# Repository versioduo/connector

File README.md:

# ⚡ V2 Link and Power connectors

# Copying
Anyone can use this public domain work without having to seek authorisation, no one can ever own it.

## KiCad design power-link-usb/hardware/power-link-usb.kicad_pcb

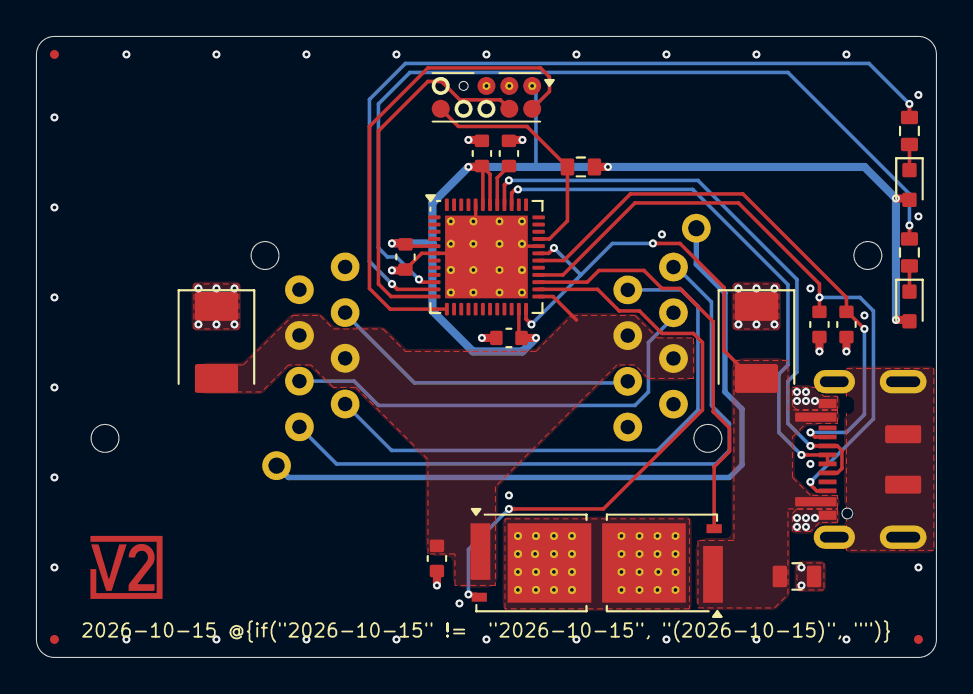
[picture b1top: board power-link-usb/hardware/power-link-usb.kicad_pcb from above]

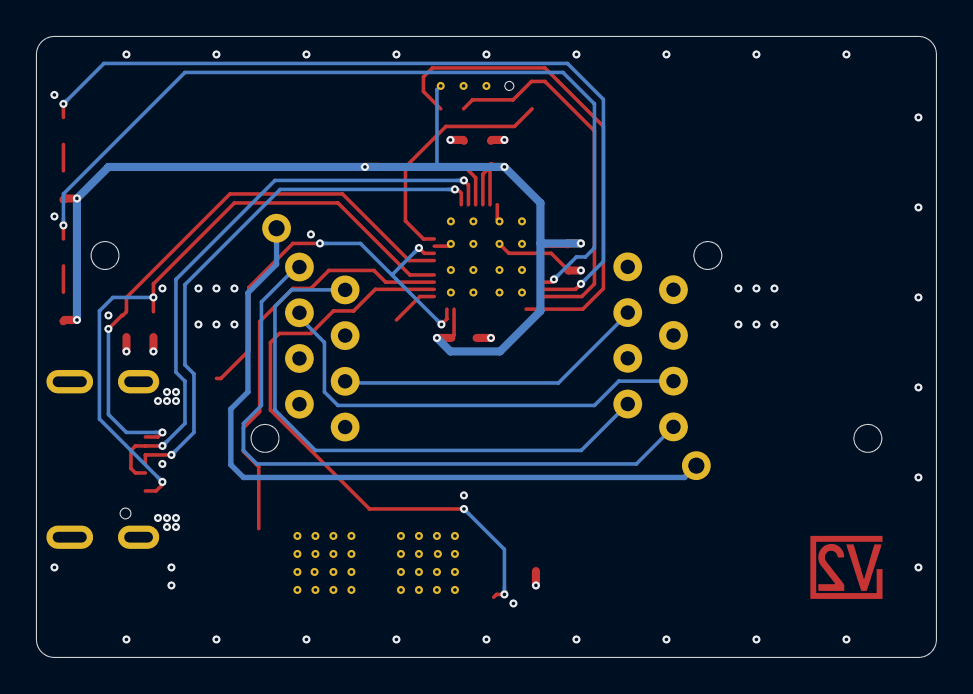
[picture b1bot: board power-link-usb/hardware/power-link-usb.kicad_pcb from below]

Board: 4 copper layers, 50.0 x 34.5 mm, 28 parts (2 on the bottom side), 24 nets.

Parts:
C201: 10u; C_1608
C202, C204, C205: 0u1; C_1608
C203: 10u; C_2012
C206: 1u; C_1608
C207, C208: 390p; C_1608
D201: Orange; LED_1608
D202: Red; LED_1608
FID101, FID102, FID103: Fiducial_Paste; Fiducial_0.5mm_Mask1mm_Paste
ICON101: V2-logo; Logo_Small
INFO101: Revision
INFO102: Layer_Numbers-4
J101, J102: NE8FAH
J201: DX07S016JA3; JAE_DX07S016JA3-PD
J202: Cortex
Q201, Q202: BSC010N04LS; TDSON-8-FL
R201, R202: 330R; R_1608
R203: 10k; R_1608
TVS101, TVS201: SMBJ33CA; D_SMB
U201: CYPM1311-48LDXI; QFN-48-1EP_6x6mm_P0.4mm_EP4.6x4.6mm

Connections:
/+VLINK: C206.1, J101.4, J101.5, J102.4, J102.5, Q202.1 (S), TVS101.2 (A), U201.25 (VBUS_OUT_NGDO)
/Power USB/+VBUS: C203.1, J201.V (VBUS), Q201.1 (S), TVS201.2 (A), U201.24 (VBUS_IN_NGDO), U201.31 (VBUS_C)
/Power USB/+VCORE: C205.2, U201.41 (VCCD)
/Power USB/+VSUPPLY: C201.1, C202.1, C204.1, D201.2 (A), D202.2 (A), J202.1 (VCC), R203.2, U201.5 (VDDA), U201.23 (VDDIO), U201.42 (VDDIO), U201.43 (VDDD)
/Power USB/Drain: Q201.5 (D), Q202.5 (D)
/Power USB/LED-Orange: R201.2, U201.11 (P5.5)
/Power USB/LED-Red: R202.2, U201.10 (P5.3)
/Power USB/RESET: J202.10 (RESET), R203.1, U201.33 (XRES)
/Power USB/Rail-Input: Q201.4 (G), U201.27 (VBUS_IN_CTRL)
/Power USB/Rail-Output: Q202.4 (G), U201.26 (VBUS_OUT_CTRL)
/Power USB/SWCLK: J202.4 (SWCLK), U201.12 (P1.1/SWD_CLK)
/Power USB/SWDIO: J202.2 (SWDIO), U201.13 (P1.2/SWD_IO)
/Power USB/USB+: J201.A6 (D+), J201.B6 (D+), U201.39 (USB+)
/Power USB/USB-: J201.A7 (D-), J201.B7 (D-), U201.40 (USB-)
/Power USB/USB-CC1: C207.1, J201.A5 (CC1), U201.28 (CC1)
/Power USB/USB-CC2: C208.1, J201.B5 (CC2), U201.30 (CC2)
/RX-A: J101.3, J102.3
/RX-B: J101.6, J102.6
/Shield RJ45: J101.S, J102.S
/TX-Y: J101.1, J102.1
/TX-Z: J101.2, J102.2
GND: C201.2, C202.2, C203.2, C204.2, C205.1, C206.2, C207.2, C208.2, J101.7, J101.8, J102.7, J102.8, J201.G (GND), J202.3 (GND), J202.5 (GND), TVS101.1 (K), TVS201.1 (K), U201.6 (VSS), U201.32 (VSS), U201.44 (VSS), U201.49 (PAD)
unnamed: D201.1 (K), R201.1
unnamed: D202.1 (K), R202.1

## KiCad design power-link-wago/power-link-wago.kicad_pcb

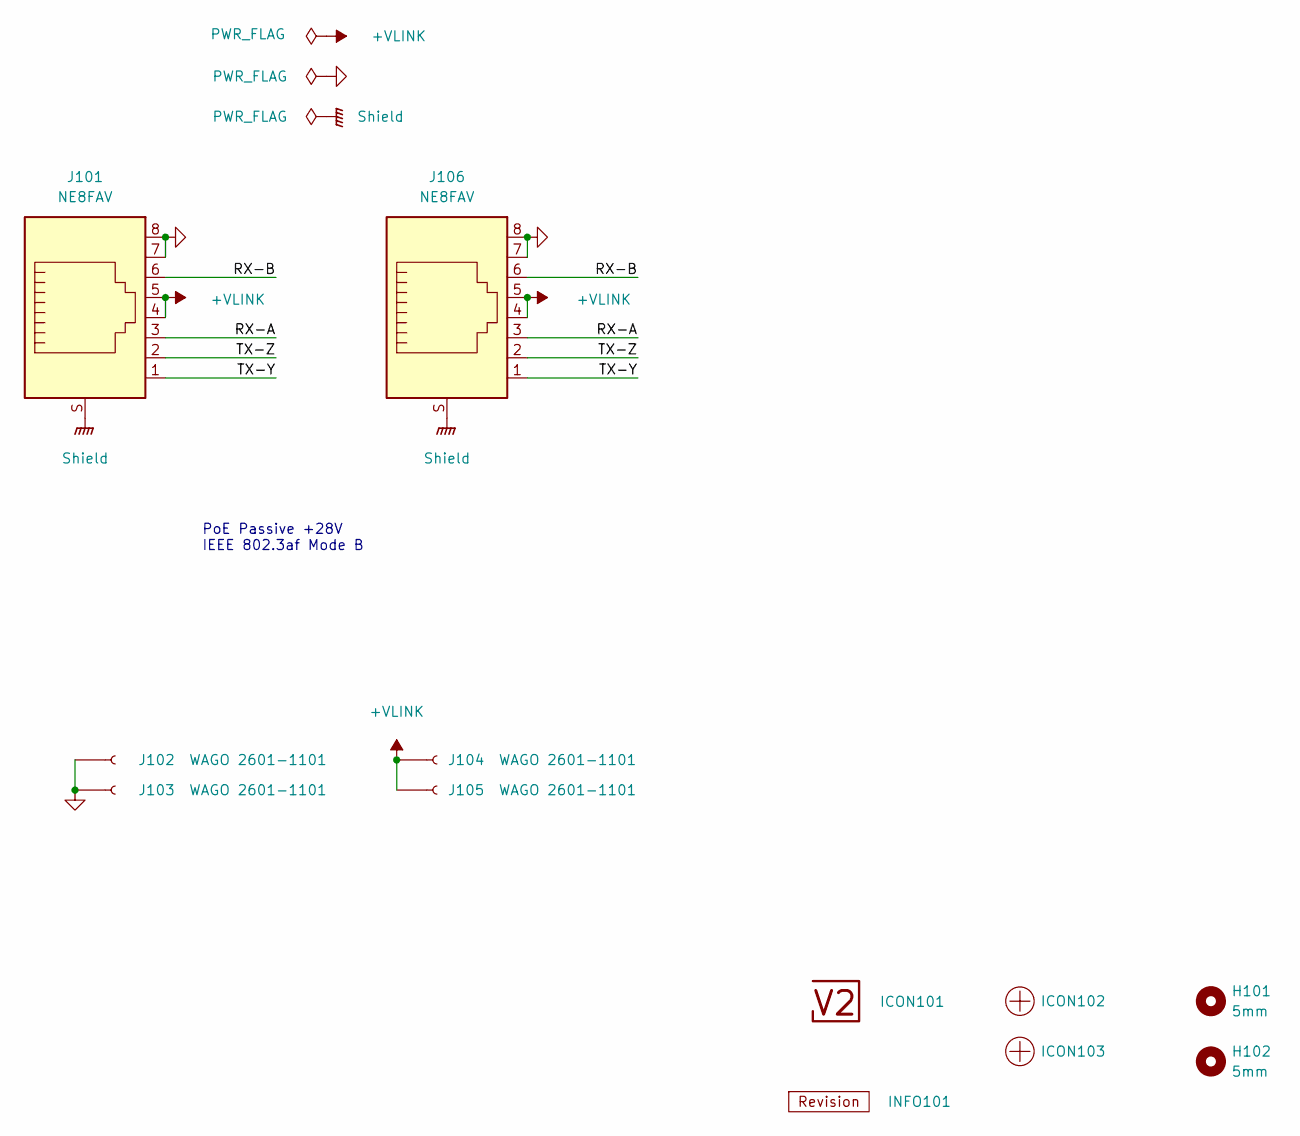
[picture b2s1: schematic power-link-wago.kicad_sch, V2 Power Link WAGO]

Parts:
H101, H102: 5mm; MountingHole_5mm
ICON101: V2-logo; Logo_Small
ICON102, ICON103: Plus; Plus_Small
INFO101: Revision
J101, J106: NE8FAV; Rating CAT5e; Mouser 568-NE8FAV-SD
J102, J103, J104, J105: WAGO 2601-1101; 2601-1101; Rating 17.5A

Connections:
/+VLINK: J101.4, J101.5, J104.1, J105.1, J106.4, J106.5
/RX-A: J101.3, J106.3
/RX-B: J101.6, J106.6
/Shield: J101.S, J106.S
/TX-Y: J101.1, J106.1
/TX-Z: J101.2, J106.2
GND: J101.7, J101.8, J102.1, J103.1, J106.7, J106.8

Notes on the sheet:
PoE Passive +28V IEEE 802.3af Mode B

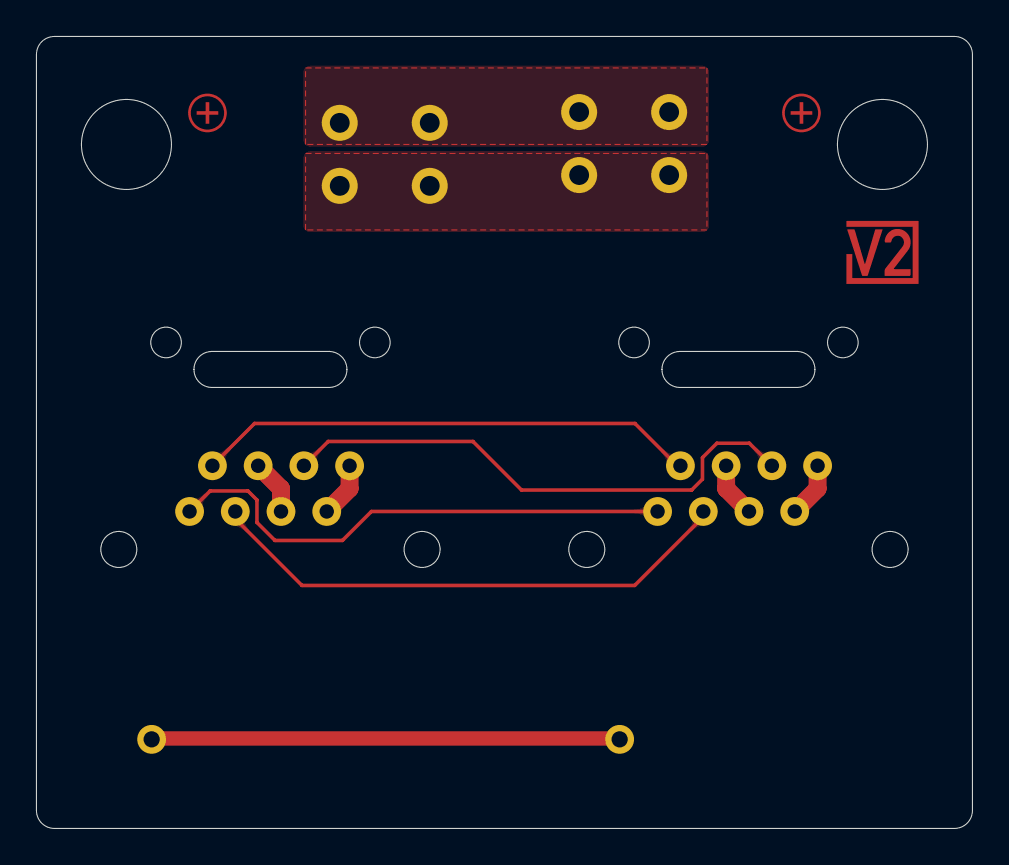
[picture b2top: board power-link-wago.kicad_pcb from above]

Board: 4 copper layers, 52.0 x 44.0 mm, 12 parts (1 on the bottom side), 7 nets.

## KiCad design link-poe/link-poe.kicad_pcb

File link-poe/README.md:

# V2 Link PoE
PoE Passive +28V
IEEE 802.3af Mode B

## Board

## Schematic
[PDF](link-poe.pdf)

## Bill Of Materials
[Interactive BOM](https://versioduo.com/view?url=https://raw.githubusercontent.com/versioduo/connector/refs/heads/main/link-poe/link-poe-bom.html)

# Copying
Anyone can use this public domain work without having to seek authorisation, no one can ever own it.

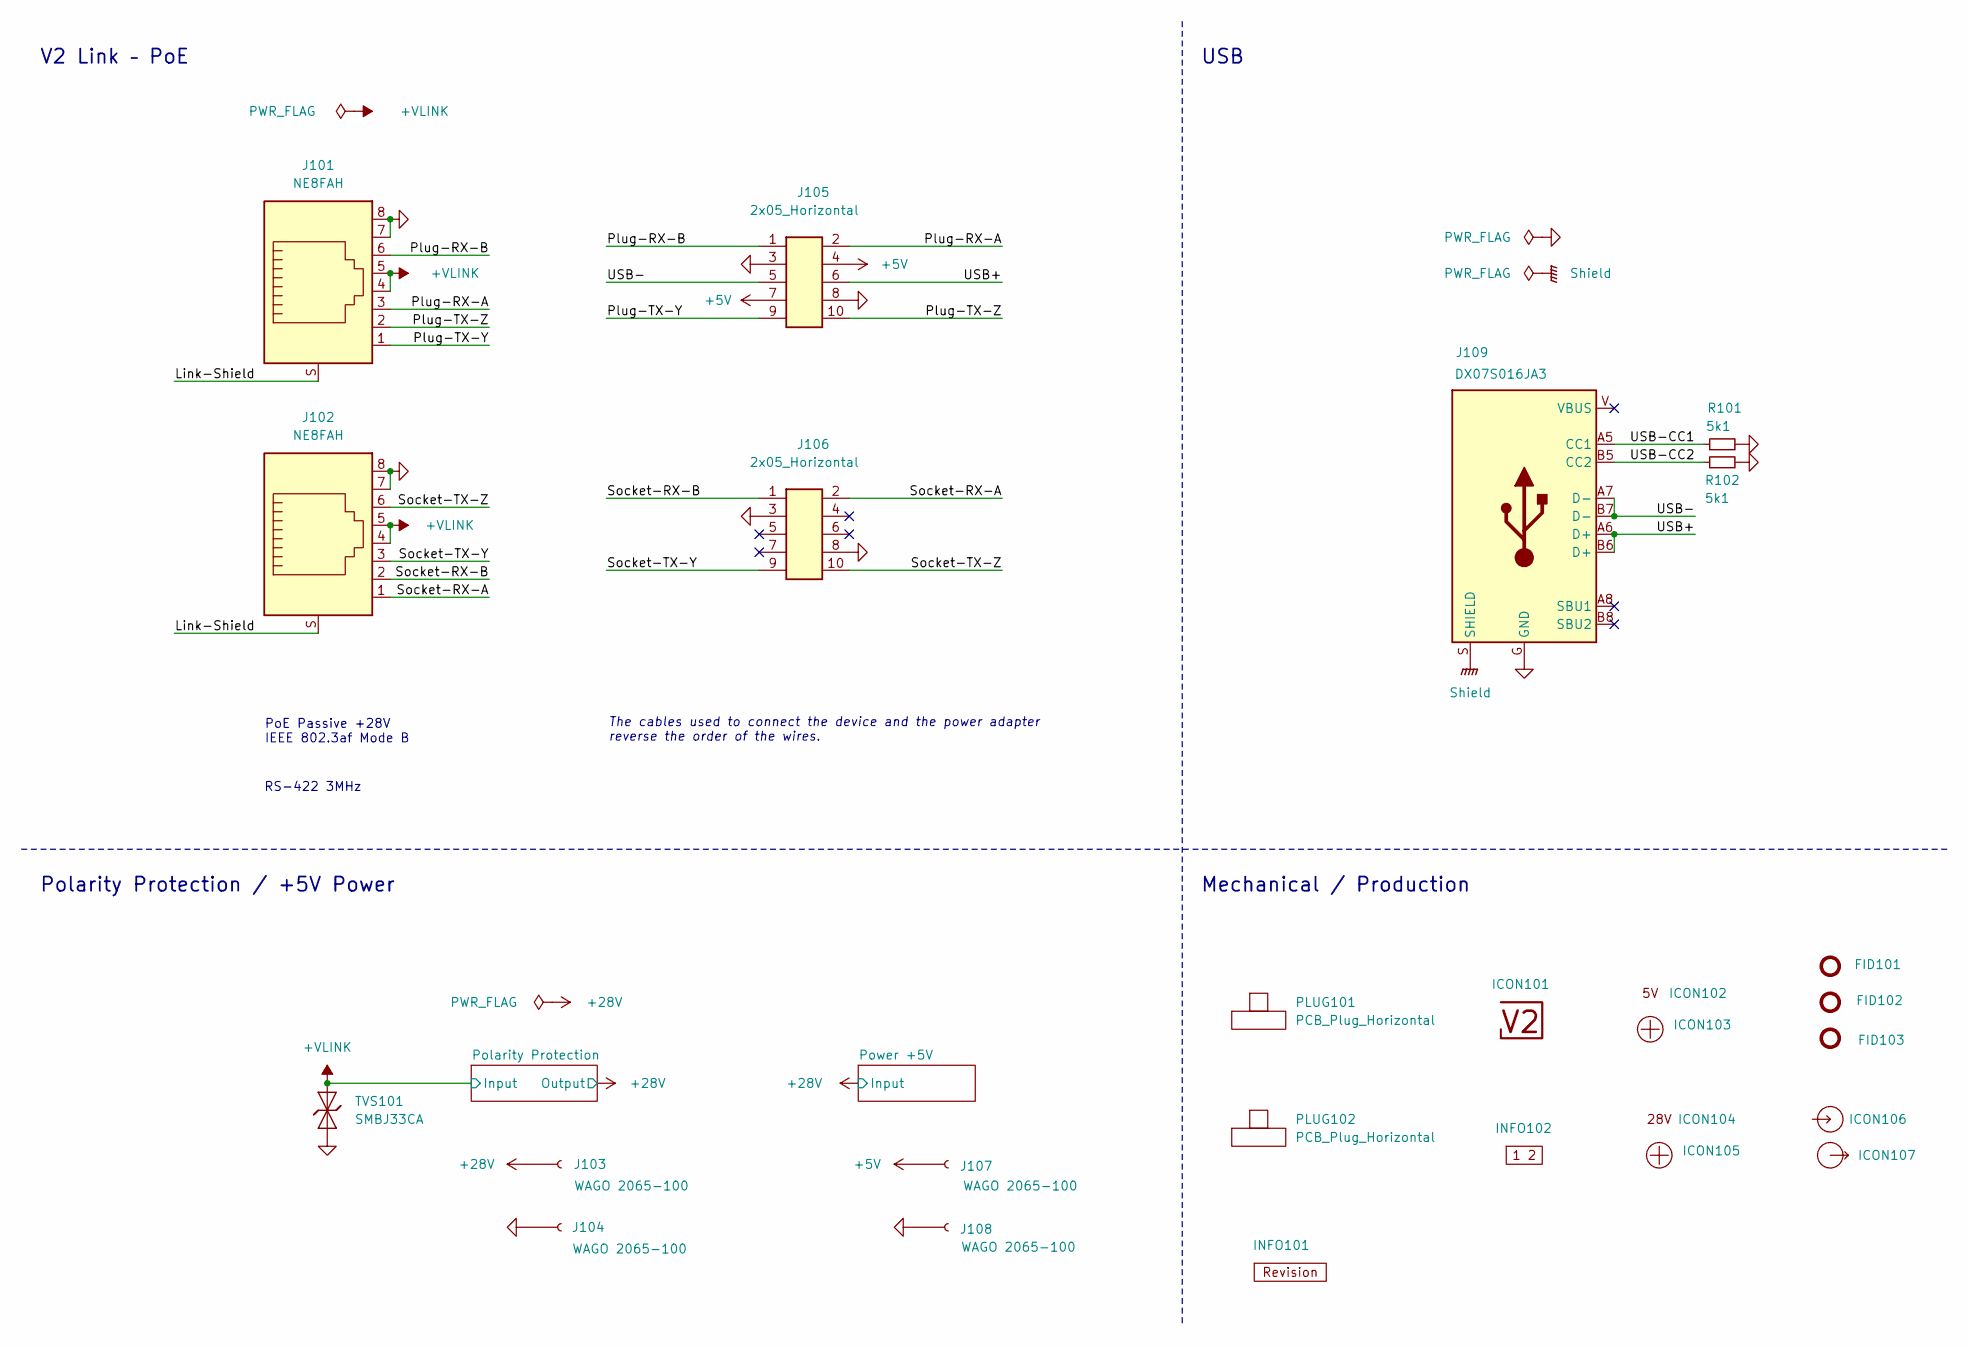
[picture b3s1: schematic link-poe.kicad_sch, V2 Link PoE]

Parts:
FID101, FID102, FID103: Fiducial_Paste; Fiducial_0.5mm_Mask1mm_Paste
ICON101: V2-logo; Logo_Small
ICON102: 5V
ICON103, ICON105: Plus; Plus_Small
ICON104: 28V
ICON106: Arrow_In
ICON107: Arrow_Out
INFO101: Revision
INFO102: Layer_Numbers-4
J101, J102: NE8FAH; Rating CAT5e; Mouser 568-NE8FAH
J103, J104, J107, J108: WAGO 2065-100; 2065-100; Rating 9A
J105, J106: 2x05_Horizontal; PinHeader_2x05_P1.27mm_Horizontal; Rating 1A; Mouser 649-200211120001T4LF
J109: DX07S016JA3; JAE_DX07S016JA3; Rating USB2.0; Mouser 656-DX07S016JA3R1500
PLUG101, PLUG102: PCB_Plug_Horizontal
R101, R102: 5k1; R_1608; Rating 100mW; Mouser 71-CRCW06035K10FKEAC
TVS101: SMBJ33CA; D_SMB; Rating 33V; Mouser 652-SMBJ33CA-Q

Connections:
+5V: J105.4, J105.7, J107.1; also elsewhere on the board
+28V: J103.1; also elsewhere on the board
/+VLINK: J101.4, J101.5, J102.4, J102.5, TVS101.2 (A); also elsewhere on the board
/Link-Shield: J101.S, J102.S
/Plug-RX-A: J101.3, J105.2
/Plug-RX-B: J101.6, J105.1
/Plug-TX-Y: J101.1, J105.9
/Plug-TX-Z: J101.2, J105.10
/Shield: J109.S (SHIELD)
/Socket-RX-A: J102.1, J106.2
/Socket-RX-B: J102.2, J106.1
/Socket-TX-Y: J102.3, J106.9
/Socket-TX-Z: J102.6, J106.10
/USB+: J105.6, J109.A6 (D+), J109.B6 (D+)
/USB-: J105.5, J109.A7 (D-), J109.B7 (D-)
/USB-CC1: J109.A5 (CC1), R101.1
/USB-CC2: J109.B5 (CC2), R102.1
GND: J101.7, J101.8, J102.7, J102.8, J104.1, J105.3, J105.8, J106.3, J106.8, J108.1, J109.G (GND), R101.2, R102.2, TVS101.1 (K); also elsewhere on the board

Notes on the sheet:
Polarity Protection / +5V Power
PoE Passive +28V IEEE 802.3af Mode B
Mechanical / Production
The cables used to connect the device and the power adapter reverse the order of the wires.
USB
V2 Link – PoE
RS-422 3MHz

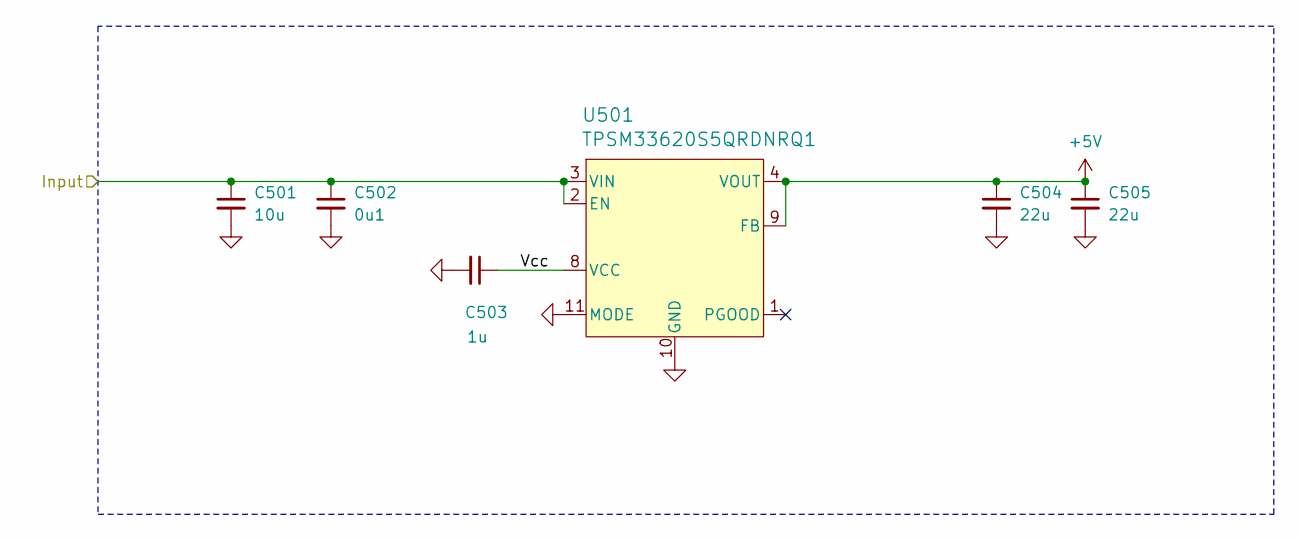
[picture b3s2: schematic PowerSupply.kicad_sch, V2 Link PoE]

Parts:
C501: 10u; C_3225; Rating 50V; Mouser 810-CNC6P1X7R1H106K2
C502: 0u1; C_1608; Rating 50V; Mouser 810-CGA3E2X7R1H104MA
C503: 1u; C_1608; Rating 50V; Mouser 810-CGA3E3X7R1H105K0
C504, C505: 22u; C_3225; Rating 25V; Mouser 810-CGA6P3X7R1E226M5
U501: TPSM33620S5QRDNRQ1; QFN-11; Rating 2A; Mouser 595-SM33620S5QRDNRQ1

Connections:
+5V: C504.1, C505.1, U501.4 (VOUT), U501.9 (FB); also elsewhere on the board
+28V: C501.1, C502.1, U501.2 (EN), U501.3 (VIN); also elsewhere on the board
/Power +5V/Vcc: C503.1, U501.8 (VCC)
GND: C501.2, C502.2, C503.2, C504.2, C505.2, U501.10 (GND), U501.11 (MODE); also elsewhere on the board

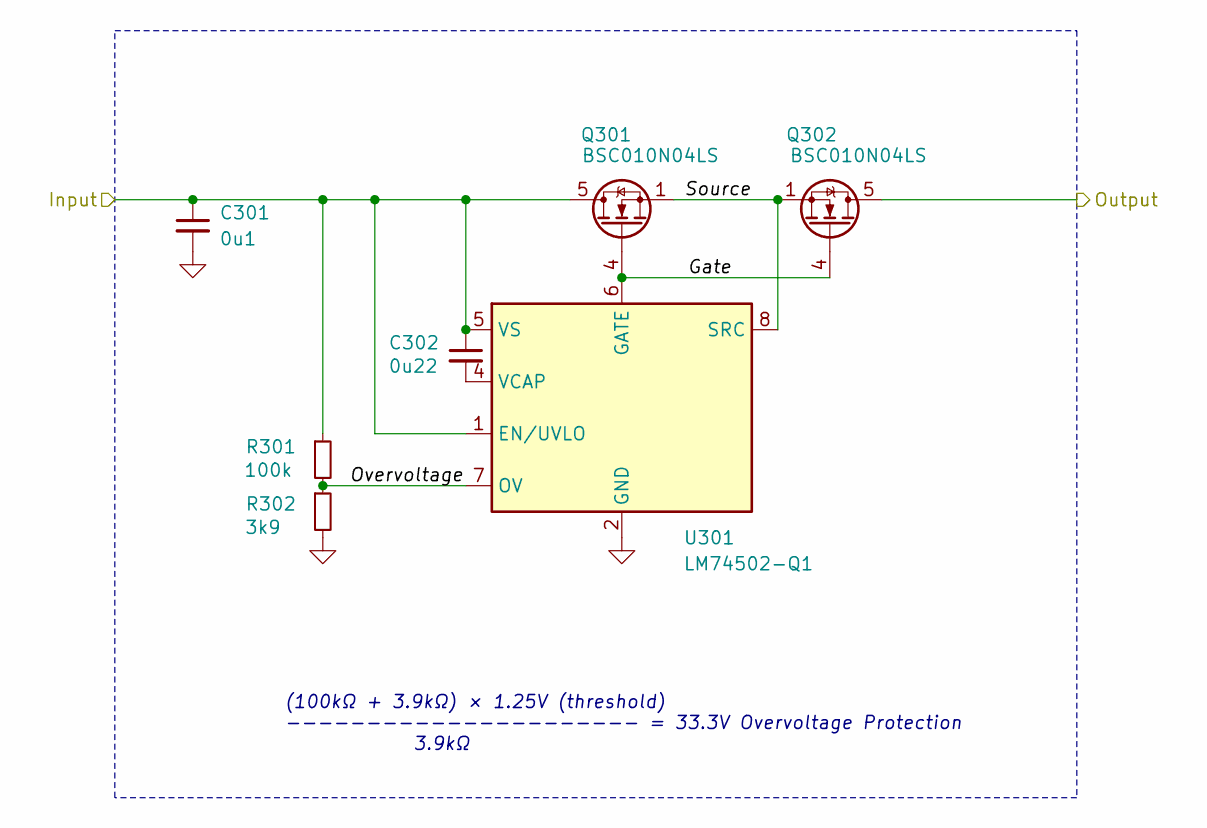
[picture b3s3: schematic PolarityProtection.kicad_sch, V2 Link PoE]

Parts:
C301: 0u1; C_1608; Rating 50V; Mouser 810-CGA3E2X7R1H104MA
C302: 0u22; C_1608; Rating 50V; Mouser 603-CC0603JRX79BB224
Q301, Q302: BSC010N04LS; TDSON-8-FL; Rating 40V; Mouser 726-BSC010N04LS
R301: 100k; R_1608; Rating 100mW; Mouser 71-CRCW0603100KFKEAC
R302: 3k9; R_1608; Rating 100mW; Mouser 71-CRCW06033K90FKEAC
U301: LM74502-Q1; SOT-23-8; Rating 60uA; Mouser 595-LM74502QDDFRQ1

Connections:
+28V: Q302.5 (D); also elsewhere on the board
/+VLINK: C301.1, C302.1, Q301.5 (D), R301.1, U301.1 (EN/UVLO), U301.5 (VS); also elsewhere on the board
/Polarity Protection/Gate: Q301.4 (G), Q302.4 (G), U301.6 (GATE)
/Polarity Protection/Overvoltage: R301.2, R302.1, U301.7 (OV)
/Polarity Protection/Source: Q301.1 (S), Q302.1 (S), U301.8 (SRC)
GND: C301.2, R302.2, U301.2 (GND); also elsewhere on the board
unnamed: C302.2, U301.4 (VCAP)

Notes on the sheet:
(100kΩ + 3.9kΩ) × 1.25V (threshold) ---------------------- = 33.3V Overvoltage Protection 3.9kΩ

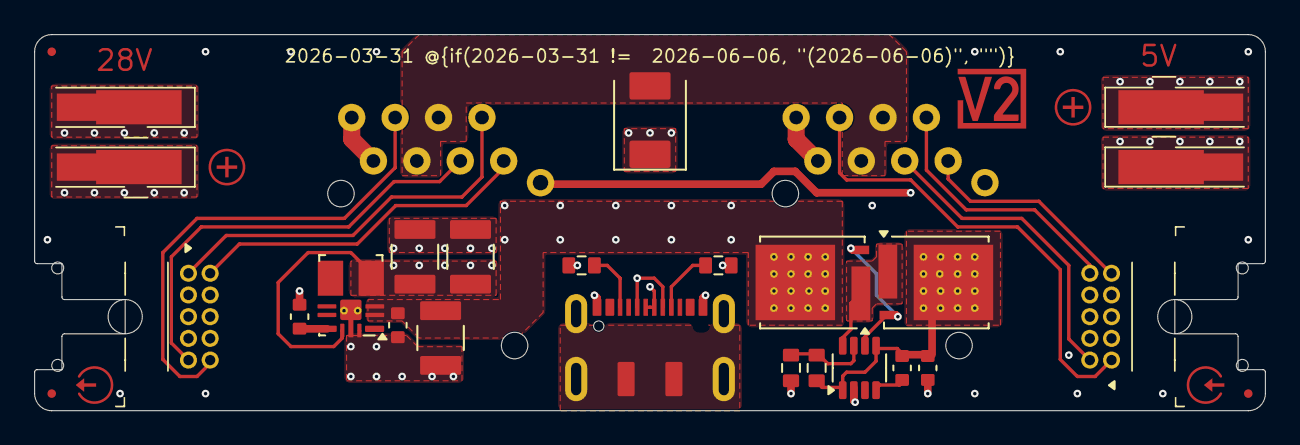
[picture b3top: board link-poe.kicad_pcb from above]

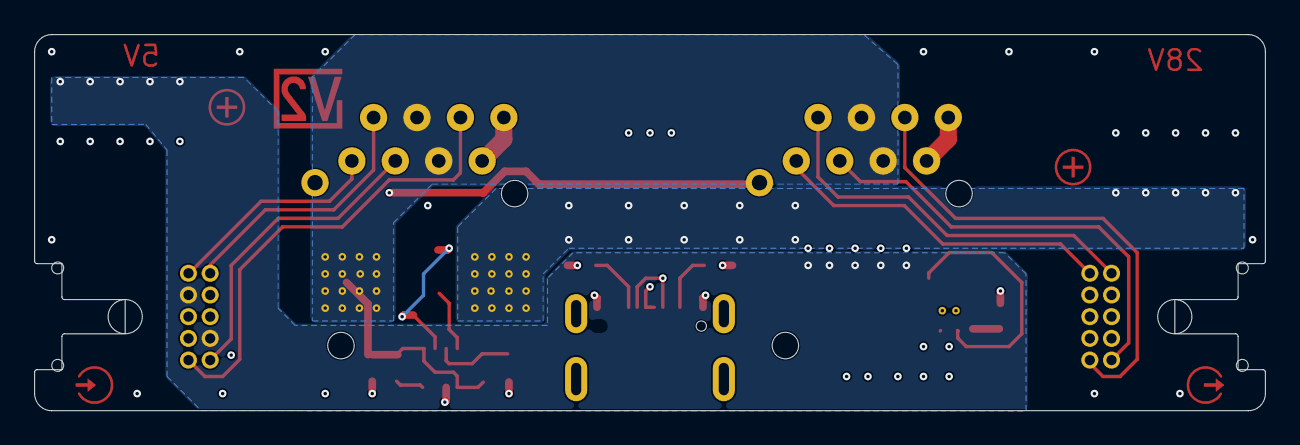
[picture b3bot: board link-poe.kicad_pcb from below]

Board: 4 copper layers, 72.0 x 22.0 mm, 39 parts (2 on the bottom side), 22 nets.

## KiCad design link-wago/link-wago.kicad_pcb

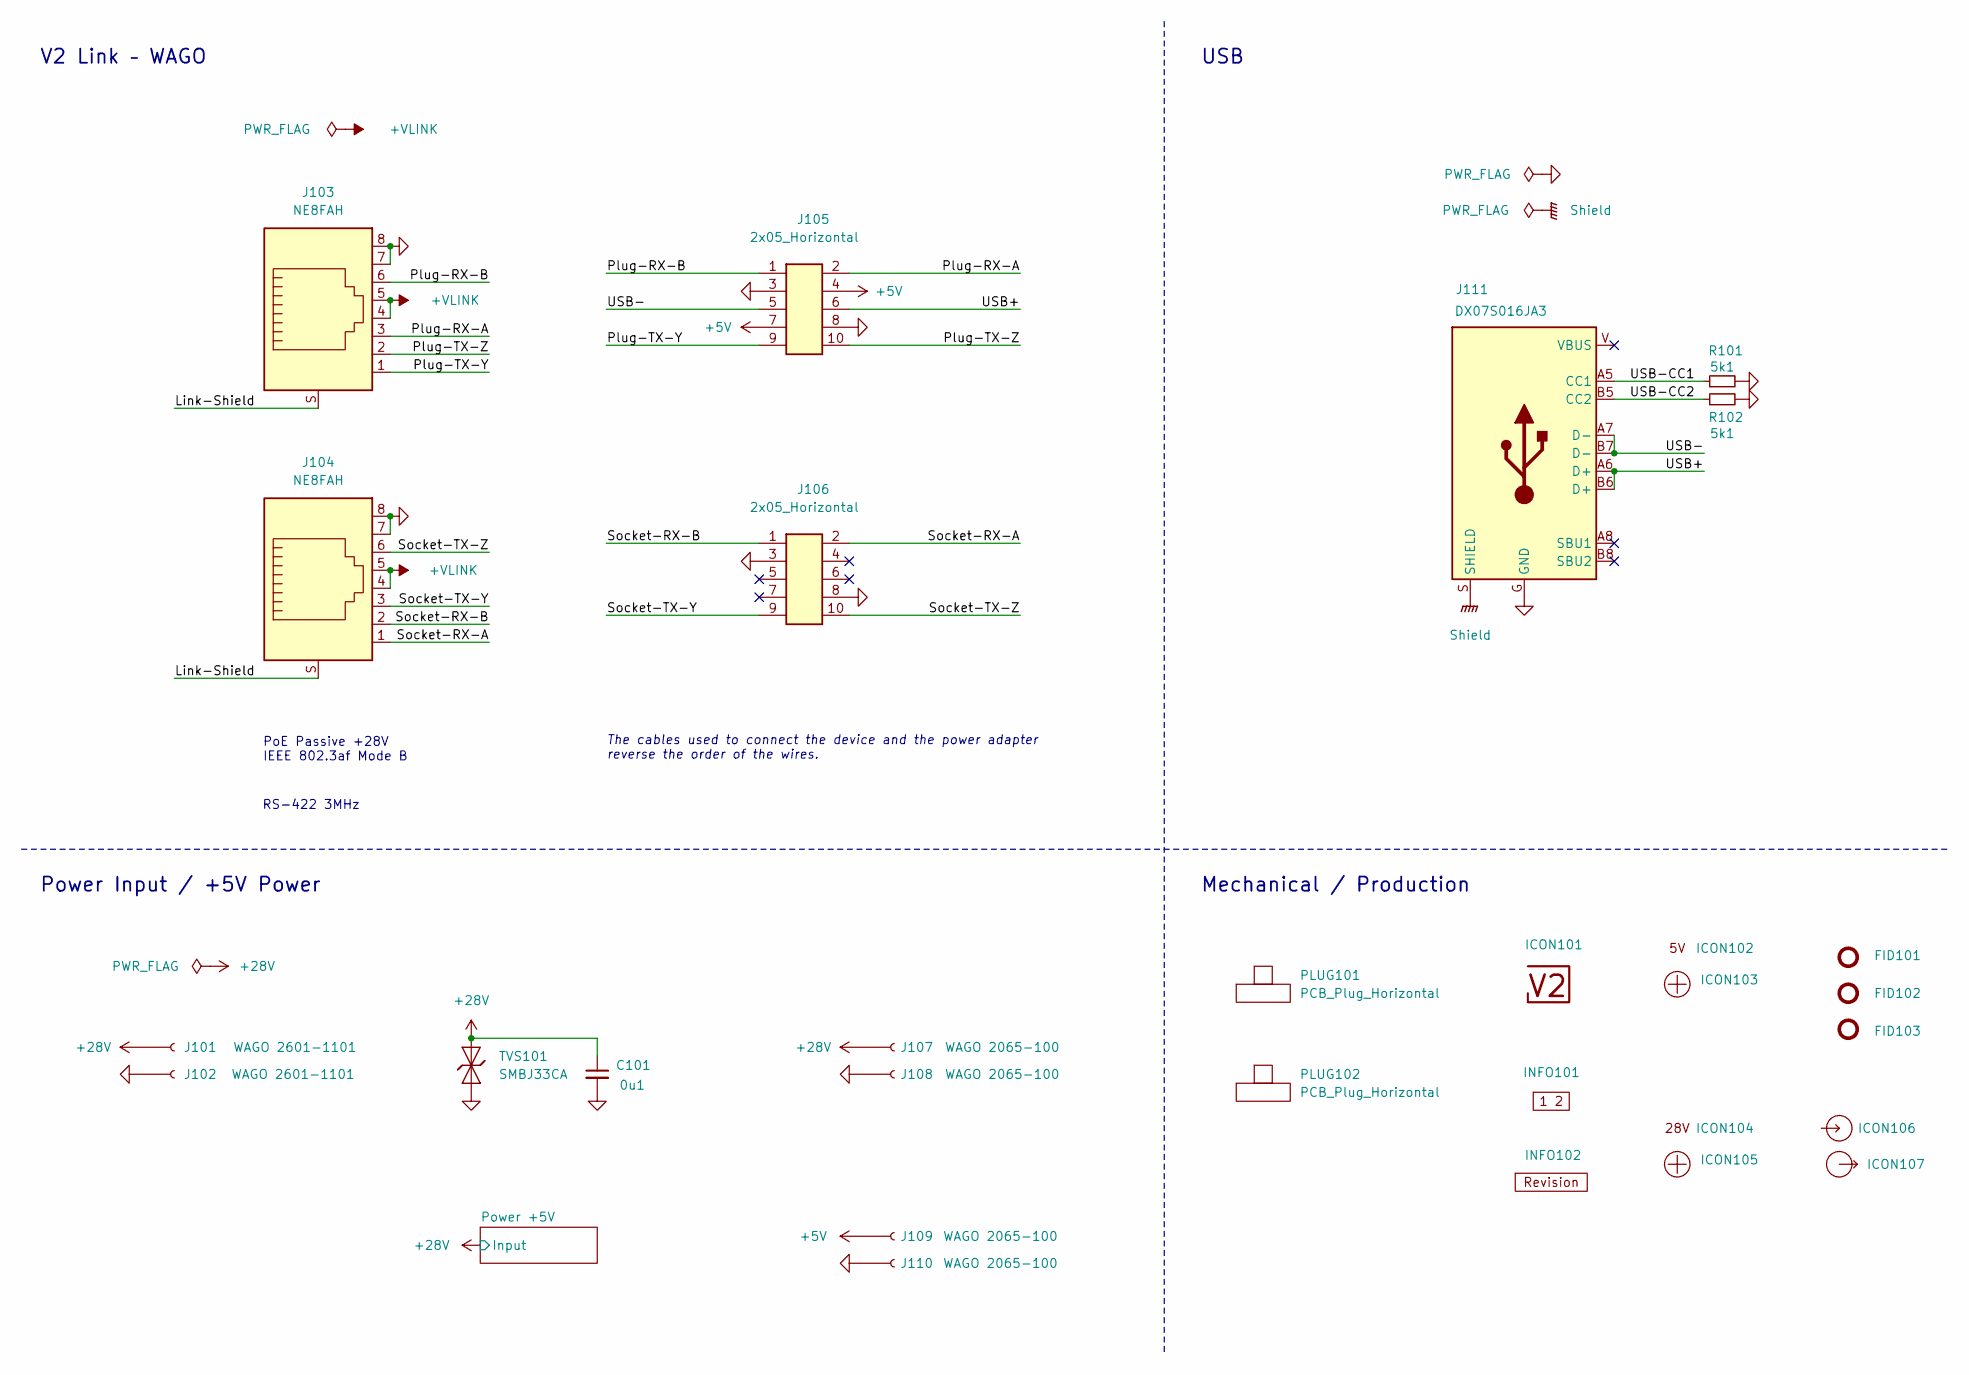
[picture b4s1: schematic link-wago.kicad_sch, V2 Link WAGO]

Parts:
C101: 0u1; C_1608; Rating 50V; Mouser 810-CGA3E2X7R1H104MA
FID101, FID102, FID103: Fiducial_Paste; Fiducial_0.5mm_Mask1mm_Paste
ICON101: V2-logo; Logo_Small
ICON102: 5V
ICON103, ICON105: Plus; Plus_Small
ICON104: 28V
ICON106: Arrow_In
ICON107: Arrow_Out
INFO101: Layer_Numbers-4
INFO102: Revision
J101, J102: WAGO 2601-1101; 2601-1101; Rating 17.5A
J103, J104: NE8FAH; Rating CAT5e; Mouser 568-NE8FAH
J105, J106: 2x05_Horizontal; PinHeader_2x05_P1.27mm_Horizontal; Rating 1A; Mouser 649-200211120001T4LF
J107, J108, J109, J110: WAGO 2065-100; 2065-100; Rating 9A
J111: DX07S016JA3; JAE_DX07S016JA3; Rating USB2.0; Mouser 656-DX07S016JA3R1500
PLUG101, PLUG102: PCB_Plug_Horizontal
R101, R102: 5k1; R_1608; Rating 100mW; Mouser 71-CRCW06035K10FKEAC
TVS101: SMBJ33CA; D_SMB; Rating 33V; Mouser 652-SMBJ33CA-Q

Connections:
+5V: J105.4, J105.7, J109.1; also elsewhere on the board
+28V: C101.1, J101.1, J107.1, TVS101.2 (A); also elsewhere on the board
/+VLINK: J103.4, J103.5, J104.4, J104.5
/Link-Shield: J103.S, J104.S
/Plug-RX-A: J103.3, J105.2
/Plug-RX-B: J103.6, J105.1
/Plug-TX-Y: J103.1, J105.9
/Plug-TX-Z: J103.2, J105.10
/Shield: J111.S (SHIELD)
/Socket-RX-A: J104.1, J106.2
/Socket-RX-B: J104.2, J106.1
/Socket-TX-Y: J104.3, J106.9
/Socket-TX-Z: J104.6, J106.10
/USB+: J105.6, J111.A6 (D+), J111.B6 (D+)
/USB-: J105.5, J111.A7 (D-), J111.B7 (D-)
/USB-CC1: J111.A5 (CC1), R101.1
/USB-CC2: J111.B5 (CC2), R102.1
GND: C101.2, J102.1, J103.7, J103.8, J104.7, J104.8, J105.3, J105.8, J106.3, J106.8, J108.1, J110.1, J111.G (GND), R101.2, R102.2, TVS101.1 (K); also elsewhere on the board

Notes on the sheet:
PoE Passive +28V IEEE 802.3af Mode B
The cables used to connect the device and the power adapter reverse the order of the wires.
RS-422 3MHz
Power Input / +5V Power
Mechanical / Production
USB
V2 Link – WAGO

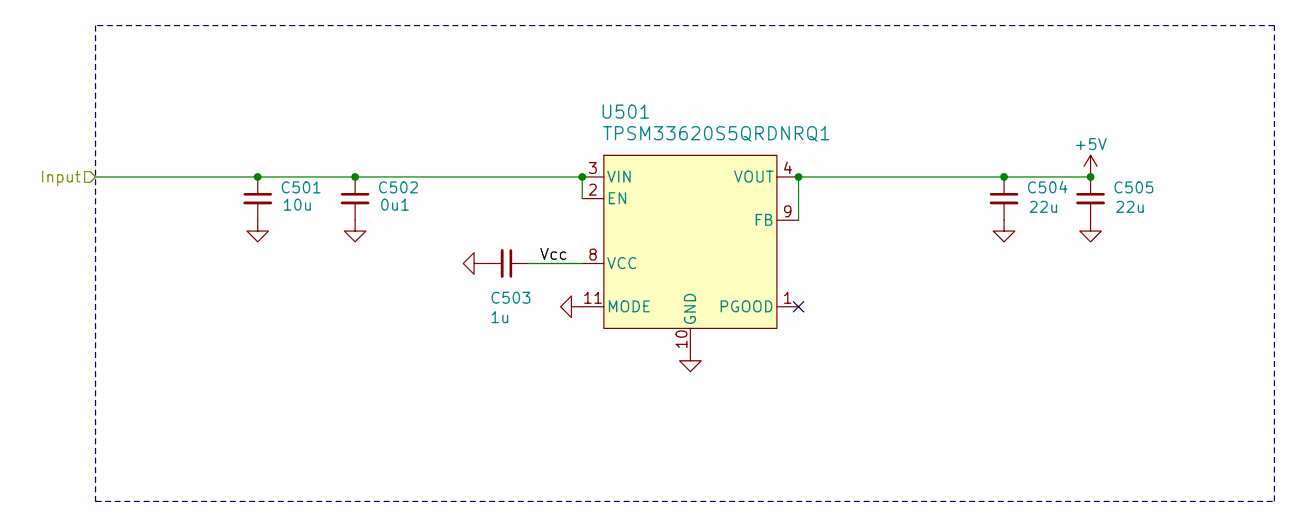
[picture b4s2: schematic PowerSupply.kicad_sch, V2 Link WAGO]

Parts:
C501: 10u; C_3225; Rating 50V; Mouser 810-CNC6P1X7R1H106K2
C502: 0u1; C_1608; Rating 50V; Mouser 810-CGA3E2X7R1H104MA
C503: 1u; C_1608; Rating 50V; Mouser 810-CGA3E3X7R1H105K0
C504, C505: 22u; C_3225; Rating 25V; Mouser 810-CGA6P3X7R1E226M5
U501: TPSM33620S5QRDNRQ1; QFN-11; Rating 2A; Mouser 595-SM33620S5QRDNRQ1

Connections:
+5V: C504.1, C505.1, U501.4 (VOUT), U501.9 (FB); also elsewhere on the board
+28V: C501.1, C502.1, U501.2 (EN), U501.3 (VIN); also elsewhere on the board
/Power +5V/Vcc: C503.1, U501.8 (VCC)
GND: C501.2, C502.2, C503.2, C504.2, C505.2, U501.10 (GND), U501.11 (MODE); also elsewhere on the board

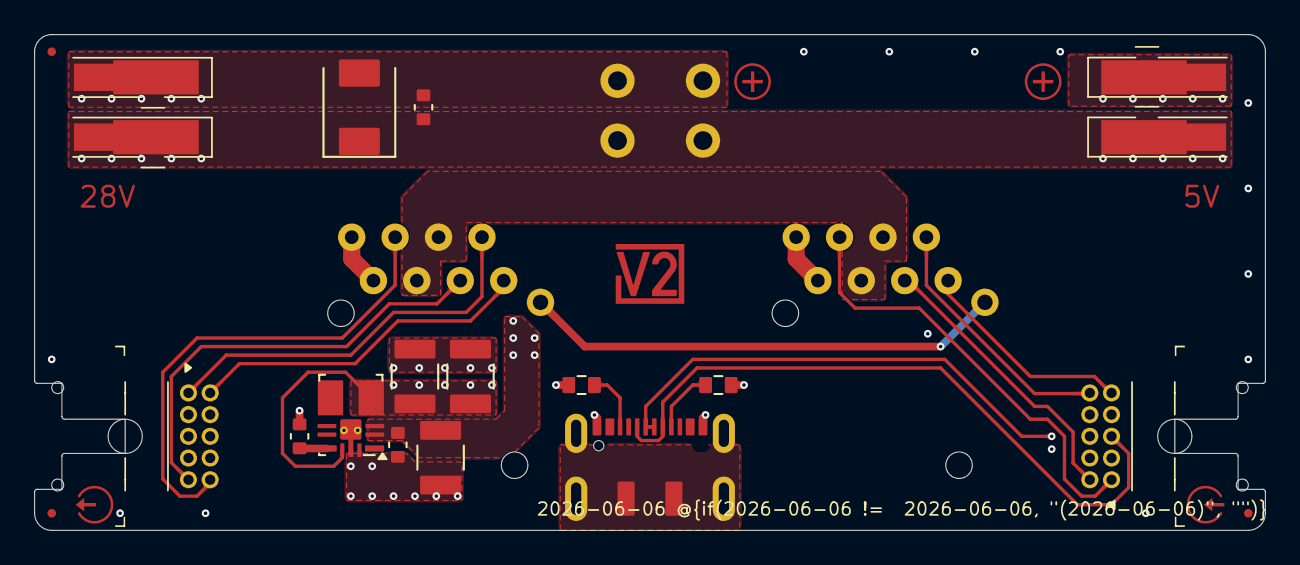
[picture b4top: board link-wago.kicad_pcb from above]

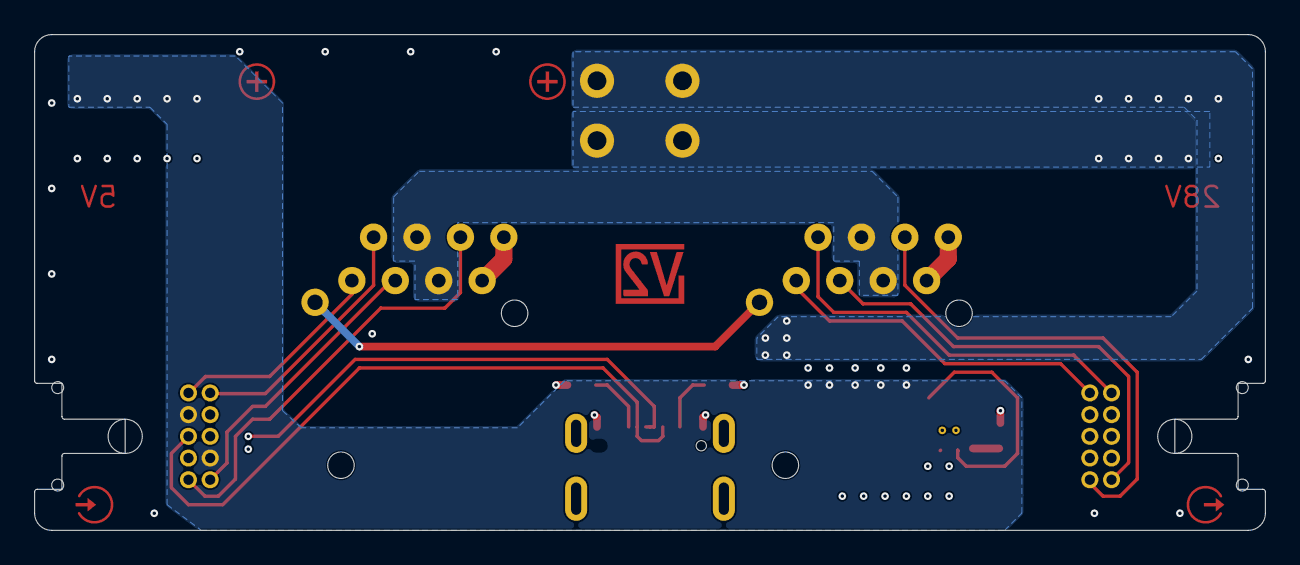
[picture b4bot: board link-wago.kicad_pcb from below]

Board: 4 copper layers, 72.0 x 29.0 mm, 35 parts (4 on the bottom side), 18 nets.

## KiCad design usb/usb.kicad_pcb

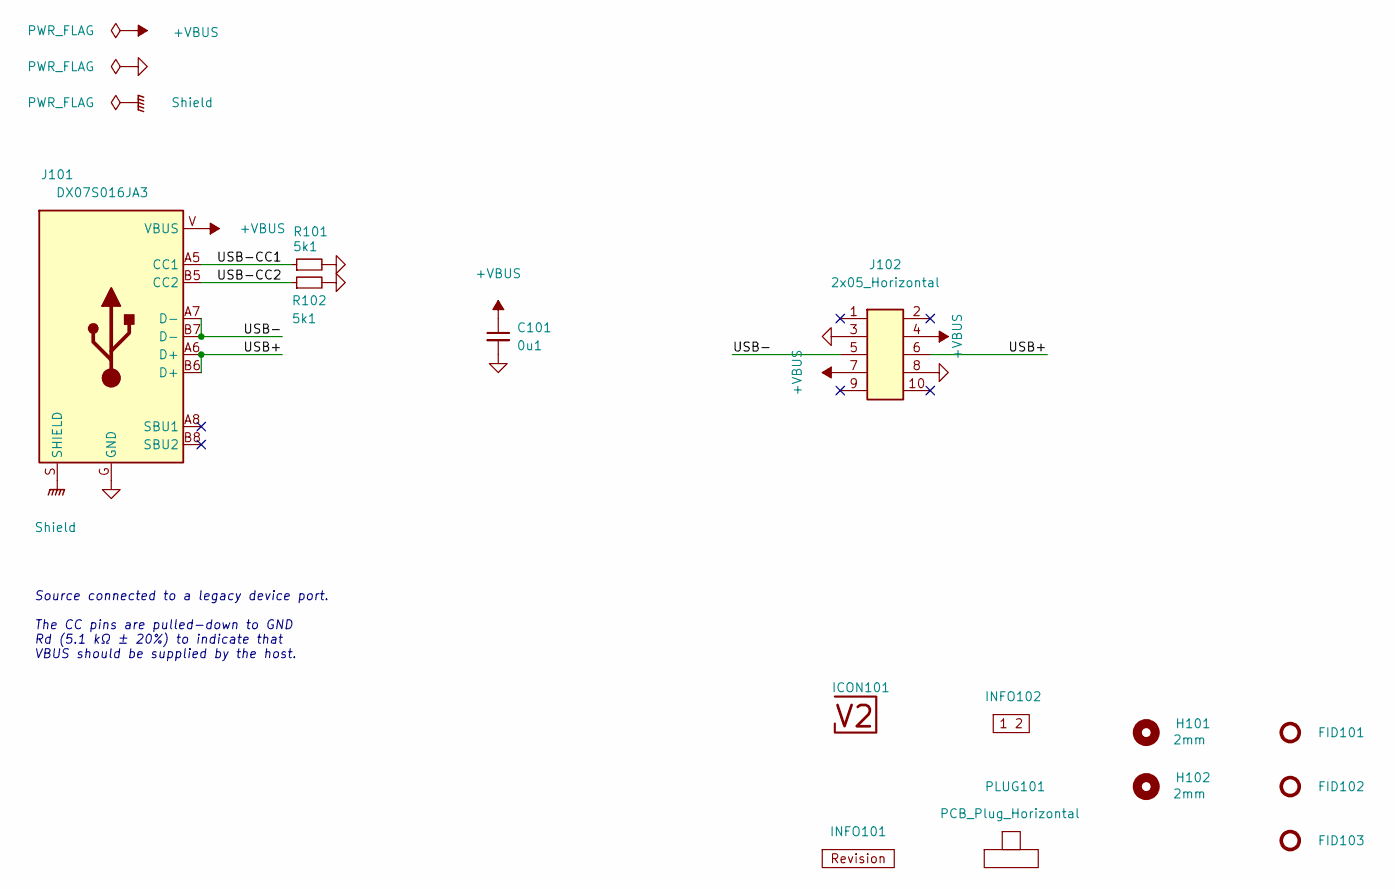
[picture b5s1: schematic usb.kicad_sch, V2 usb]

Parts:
C101: 0u1; C_1608; Rating 50V; Mouser 810-CGA3E2X7R1H104MA
FID101, FID102, FID103: Fiducial_Paste; Fiducial_0.5mm_Mask1mm_Paste
H101, H102: 2mm; MountingHole_2mm
ICON101: V2-logo; Logo_Small
INFO101: Revision
INFO102: Layer_Numbers-4
J101: DX07S016JA3; JAE_DX07S016JA3; Rating USB2.0; Mouser 656-DX07S016JA3R1500
J102: 2x05_Horizontal; PinHeader_2x05_P1.27mm_Horizontal; Rating 1A; Mouser 649-200211120001T4LF
PLUG101: PCB_Plug_Horizontal
R101, R102: 5k1; R_1608; Rating 100mW; Mouser 71-CRCW06035K10FKEAC

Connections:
/+VBUS: C101.1, J101.V (VBUS), J102.4, J102.7
/Shield: J101.S (SHIELD)
/USB+: J101.A6 (D+), J101.B6 (D+), J102.6
/USB-: J101.A7 (D-), J101.B7 (D-), J102.5
/USB-CC1: J101.A5 (CC1), R101.1
/USB-CC2: J101.B5 (CC2), R102.1
GND: C101.2, J101.G (GND), J102.3, J102.8, R101.2, R102.2

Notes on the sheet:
﻿Source connected to a legacy device port. The CC pins are pulled-down to GND Rd (5.1 kΩ ± 20%) to indicate that VBUS should be supplied by the host.

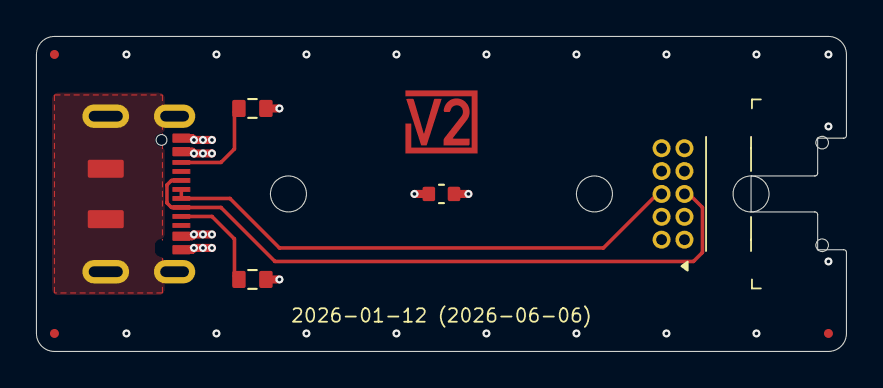
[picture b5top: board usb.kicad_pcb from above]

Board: 4 copper layers, 45.0 x 17.5 mm, 14 parts (0 on the bottom side), 6 nets.
